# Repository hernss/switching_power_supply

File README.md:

# Descripción del proyecto:

El objetivo de este proyecto es desarrollar una fuente switching de voltaje variable basada en el integrado TPS54331 de Texas Instruments. Como entrada vamos a poder utilizar una fuente ATX estándar de PC o una fuentes del estilo notebook de hasta 24 volts. La fuente proveerá una salida variable entre 1.5 volts y 24 volts la cual es ajustada mediante un potenciómetro. En el caso de alimentarse con una fuente ATX también se va a disponer de las salidas de 3,3v +5v + 12v -5v -12v.
La salida esta implementadas con borneras en dos piezas, quedando el macho adherido al PCB y una parte removible a la cual se podrán conectar cables mediante tornillos.

# Calculo de los componentes:
## Bloqueo por bajo voltaje de entrada:

* R1=  (V_START- V_STOP)/(3µA)=(6.8V-6.5V)/(3µA)=100KΩ
* R2=V_EN/((V_START- V_EN)/R1+1µA)=1.25V/((6.8V-1.25V)/100KΩ+1µA)=22123Ω

Asumo R2 = 22KΩ

## Arranque Suave:

T_SS (ms)=(C_SS (nF)x V_REF (V))/(I_SS (mA))=(10 x 0.8)/2=4 ms

## Calculo de R5 y R6:

Según la hoja de datos recomienda utilizar una resistencia de alrededor de 10K para R5, por esto asumimos inicialmente a R5 como 10K

R6 la calculamos según la siguiente ecuación:

R6=(R5 x V_REF)/(V_OUT-V_REF )

## Para obtener 4.5V a la salida:

R6=(10KΩ x 0.8V)/(4.5V-0.8V)=2162Ω 

Asumo R6 = 2.2KΩ por ser el valor comercial más cercano.

V_OUT=V_REF  x (R5/R6+1)=0.8V x (10KΩ/2.2KΩ+1)=4.44V

## Para obtener 6V a la salida:
R6=(10KΩ x 0.8V)/(6V-0.8V)=1538Ω

Como el valor comercial más cercano está muy lejos del valor que necesitamos vamos a cambiar R5 a 12K y vamos a repetir los cálculos.

R6=(12KΩ x 0.8V)/(6V-0.8V)=1845Ω

Asumo R6 = 1,8KΩ  por ser el valor comercial más cercano.

V_OUT=V_REF  x (R5/R6+1)=0.8V x (12KΩ/1.8KΩ+1)=6.13V

## Valores máximos y mínimos de la tensión de salida:

Si ahora tomamos fijo R5 = 10K y agregamos un potenciómetro de 10K con una resistencia de 330Ω en serie podemos calcular el voltaje máximo y mínimo que podemos tener a la salida.

V_MAX=V_REF  x (R5/〖R6〗_MIN +1)=0.8V x (10KΩ/330Ω+1)=25.04V

V_MIN=V_REF  x (R5/〖R6〗_MAX +1)=0.8V x (10KΩ/10330Ω+1)=1.57V

Cabe aclarar que para obtener el VMAX a la salida, la entrada tiene que tener el voltaje suficiente.

# Diagrama Esquemático:

# Circuito impreso

# Vista 3D de la placa terminada

# Panelizado del PCB

# Diseño del gabinete

# Link a ON-Shape:

https://cad.onshape.com/documents/020dfdbda6882e2ac2e1fa2c/w/ac47c3931b7ff00251a716d9/e/94a10833bc3fe93f9d4dad91

# Lista de Materiales (BOM):

Cantidad	Referencia	Fabricante	Fabricante P/N	Digikey P/N

1	C1	Panasonic Electronic Components	EEE-HB1V100R	PCE4153CT-ND

1	C2	AVX Corporation	08055C104KAT2A	478-1395-1-ND

2	C3, C4	Yageo	CC0805KRX7R9BB103	311-1136-1-ND

1	C5	Samsung Electro-Mechanics	CL21B102KBANNNC	1276-1020-1-ND

1	C6	Samsung Electro-Mechanics	CL21C470JBANNNC	1276-1156-1-ND

1	C7	KEMET	T491X107K025AT	399-8410-1-ND

3	D1, D2, D3	Diodes Incorporated	B340B-13-F	B340B-FDICT-ND

1	D4	Lite-On Inc.	LTST-C170KGKT	160-1414-1-ND

1	D5	Lite-On Inc.	LTST-C171KRKT	160-1427-2-ND

1	J1	CUI Devices	PJ-002A	CP-002A-ND

1	J2	Molex	39299242	WM7334-ND

2	J3, J6	TE Connectivity AMP Connectors	796644-2	A98248-ND

2	J4, J5	TE Connectivity AMP Connectors	796644-3	A98249-ND

1	L1	Bourns Inc.	SRR1260-150M	SRR1260-150MCT-ND

2	MP1, MP2	Visual Communications Company	LFB063CTP	LFB063CTP-ND

1	R1	Yageo	RC0805JR-07100KL	311-100KARCT-ND

1	R2	Yageo	RC0805JR-0722KL	311-22KARCT-ND

1	R3	Yageo	RC0805FR-0729K4L	311-29.4KCRTR-ND

3	R4, R6, R7	Yageo	RC0805JR-07330RL	311-330RARCT-ND

1	R5	Yageo	RC0805JR-0710KL	311-10KARCT-ND

1	RV1	Bourns Inc.	PTV111-3415A-B103	PTV111-3415A-B103-ND

1	SW1	E-Switch	TL2230EEF140	EG6031-ND

1	U1	Texas Instruments	TPS54331DDAR	296-39419-1-ND

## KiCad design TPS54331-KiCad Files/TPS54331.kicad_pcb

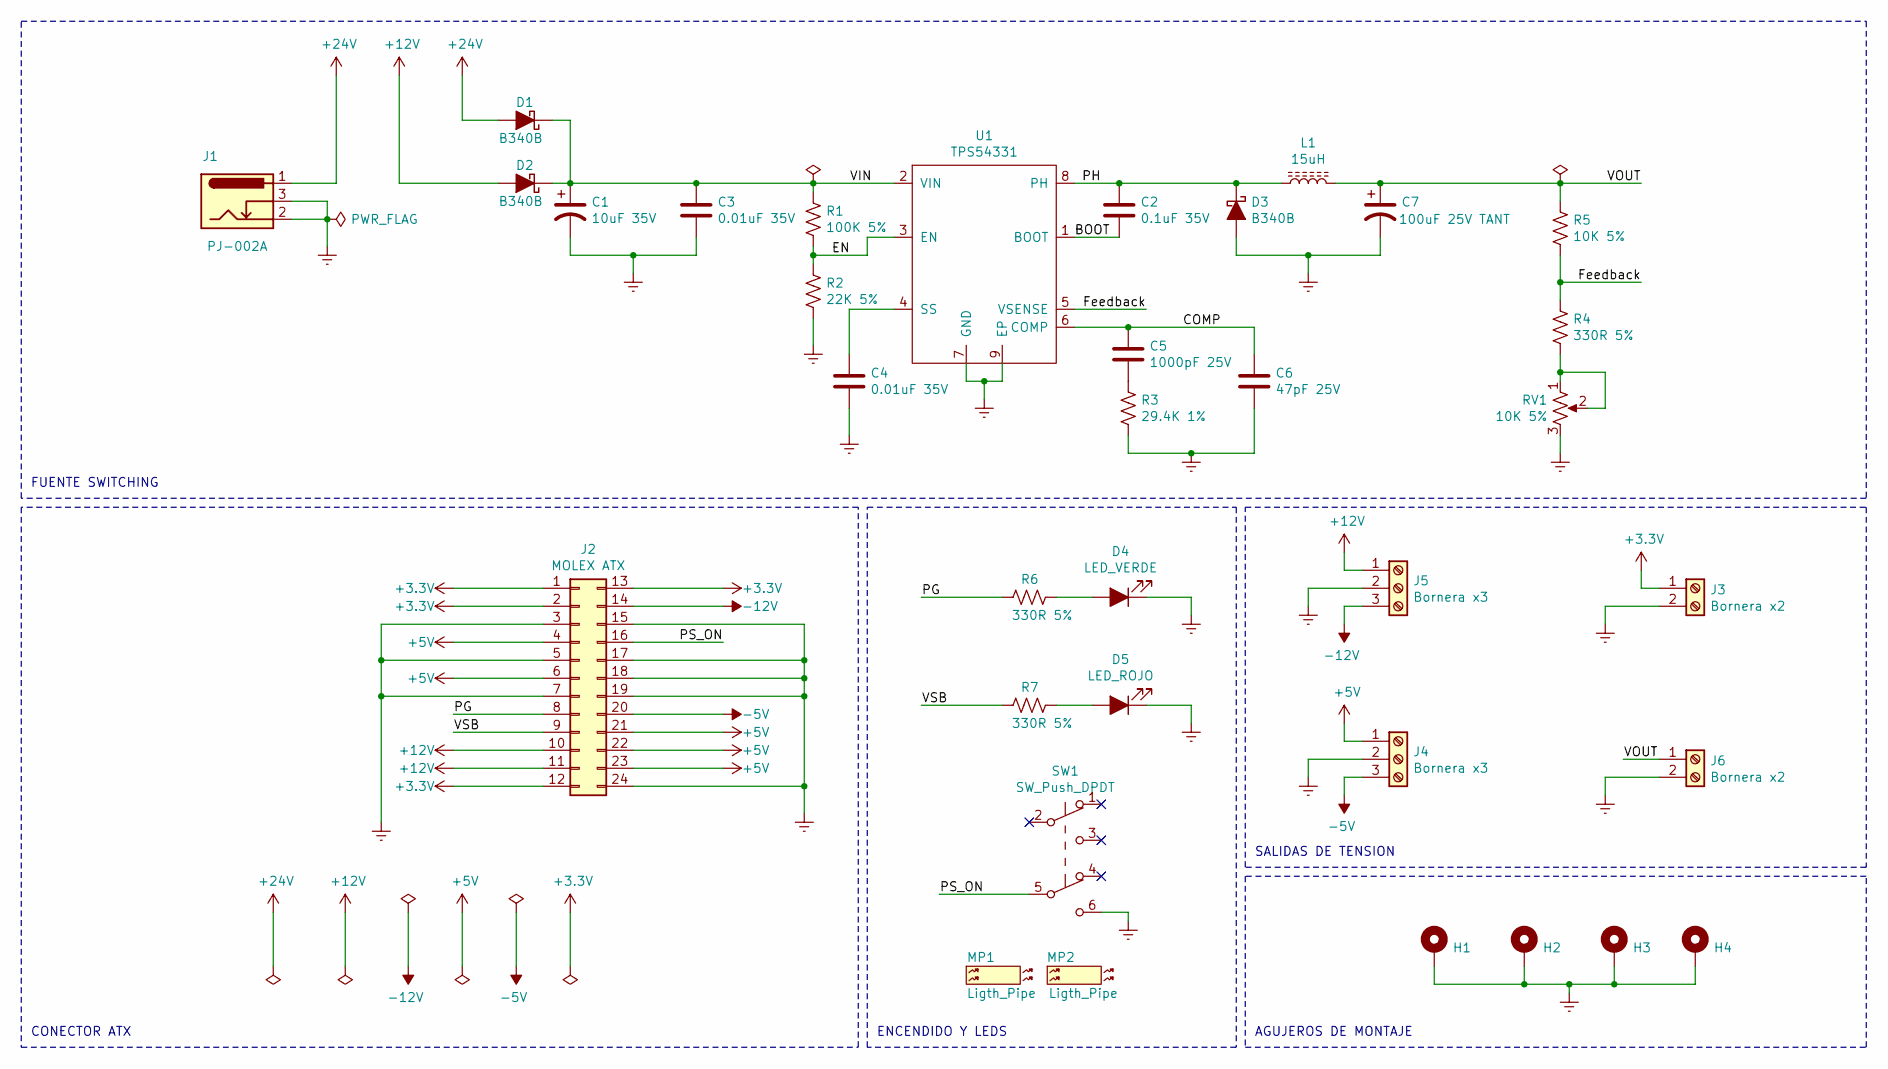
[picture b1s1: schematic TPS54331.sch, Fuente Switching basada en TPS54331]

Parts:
C1: 10uF 35V; CP_Elec_5x5.8; Manufacturer P/N EEE-HB1V100R; Digikey P/N PCE4153CT-ND
C2: 0.1uF 35V; C_0805_2012Metric; Manufacturer P/N 08055C104KAT2A; Digikey P/N 478-1395-1-ND
C3, C4: 0.01uF 35V; C_0805_2012Metric; Manufacturer P/N CC0805KRX7R9BB103; Digikey P/N 311-1136-1-ND
C5: 1000pF 25V; C_0805_2012Metric; Manufacturer P/N CL21B102KBANNNC; Digikey P/N 1276-1020-1-ND
C6: 47pF 25V; C_0805_2012Metric; Manufacturer P/N CL21C470JBANNNC; Digikey P/N 1276-1156-1-ND
C7: 100uF 25V TANT; CP_EIA-7343-43_Kemet-X; Manufacturer P/N T491X107K025AT; Digikey P/N 399-8410-1-ND
D1, D2, D3: B340B; D_SMB; Manufacturer P/N B340B-13-F; Digikey P/N B340B-FDICT-ND
D4: LED_VERDE; LED_0805_2012Metric; Manufacturer P/N LTST-C170KGKT; Digikey P/N 160-1414-1-ND
D5: LED_ROJO; LED_0805_2012Metric; Manufacturer P/N LTST-C171KRKT; Digikey P/N 160-1427-2-ND
H1, H2, H3, H4: MountingHole_Pad; MountingHole_3.2mm_M3_Pad
J1: PJ-002A; Manufacturer P/N PJ-002A; Digikey P/N CP-002A-ND
J2: MOLEX ATX; Molex_0039301240; Manufacturer P/N 0039299242; Digikey P/N WM7334-ND
J3, J6: Bornera x2; 796644-2; Manufacturer P/N 796644-2; Digikey P/N A98248-ND
J4, J5: Bornera x3; 796644-3; Manufacturer P/N 796644-3; Digikey P/N A98249-ND
L1: 15uH; SRR1260; Manufacturer P/N SRR1260-150M; Digikey P/N SRR1260-150MCT-ND
MP1, MP2: Ligth_Pipe; NoFootprint; Manufacturer P/N LFB063CTP; Digikey P/N LFB063CTP-ND
R1: 100K 5%; R_0805_2012Metric; Manufacturer P/N RC0805JR-07100KL; Digikey P/N 311-100KARCT-ND
R2: 22K 5%; R_0805_2012Metric; Manufacturer P/N RC0805JR-0722KL; Digikey P/N 311-22KARCT-ND
R3: 29.4K 1%; R_0805_2012Metric; Manufacturer P/N RC0805FR-0729K4L; Digikey P/N 311-29.4KCRTR-ND
R4, R6, R7: 330R 5%; R_0805_2012Metric; Manufacturer P/N RC0805JR-07330RL; Digikey P/N 311-330RARCT-ND
R5: 10K 5%; R_0805_2012Metric; Manufacturer P/N RC0805JR-0710KL; Digikey P/N 311-10KARCT-ND
RV1: 10K 5%; PTV111-3; Manufacturer P/N PTV111-3415A-B103; Digikey P/N PTV111-3415A-B103-ND
SW1: SW_Push_DPDT; TL2230; Manufacturer P/N TL2230EEF140; Digikey P/N EG6031-ND
U1: TPS54331; SOIC-8-1EP_3.9x4.9mm_P1.27mm_EP2.29x3mm; Manufacturer P/N TPS54331DDAR; Digikey P/N 296-39419-1-ND

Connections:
+3V3: J2.1, J2.2, J2.12, J2.13, J3.1
+5V: J2.4, J2.6, J2.21, J2.22, J2.23, J4.1
+12V: D2.2 (A), J2.10, J2.11, J5.1
+24V: D1.2 (A), J1.1
-5V: J2.20, J4.3
-12V: J2.14, J5.3
/BOOT: C2.2, U1.1 (BOOT)
/COMP: C5.1, C6.1, U1.6 (COMP)
/EN: R1.2, R2.1, U1.3 (EN)
/Feedback: R4.1, R5.2, U1.5 (VSENSE)
/PG: J2.8, R6.2
/PH: C2.1, D3.1 (K), L1.1, U1.8 (PH)
/PS_ON: J2.16, SW1.5 (B)
/VIN: C1.1, C3.1, D1.1 (K), D2.1 (K), R1.1, U1.2 (VIN)
/VOUT: C7.1, J6.1, L1.2, R5.1
/VSB: J2.9, R7.2
Earth: C1.2, C3.2, C4.2, C6.2, C7.2, D3.2 (A), D4.1 (K), D5.1 (K), H1.1, H2.1, H3.1, H4.1, J1.2, J1.3, J2.3, J2.5, J2.7, J2.15, J2.17, J2.18, J2.19, J2.24, J3.2, J4.2, J5.2, J6.2, R2.2, R3.2, RV1.3, SW1.6 (C), U1.7 (GND), U1.9 (EP)
unnamed: C4.1, U1.4 (SS)
unnamed: C5.2, R3.1
unnamed: D4.2 (A), R6.1
unnamed: D5.2 (A), R7.1
unnamed: R4.2, RV1.1, RV1.2

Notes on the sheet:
ENCENDIDO Y LEDS
CONECTOR ATX
FUENTE SWITCHING
SALIDAS DE TENSION
AGUJEROS DE MONTAJE

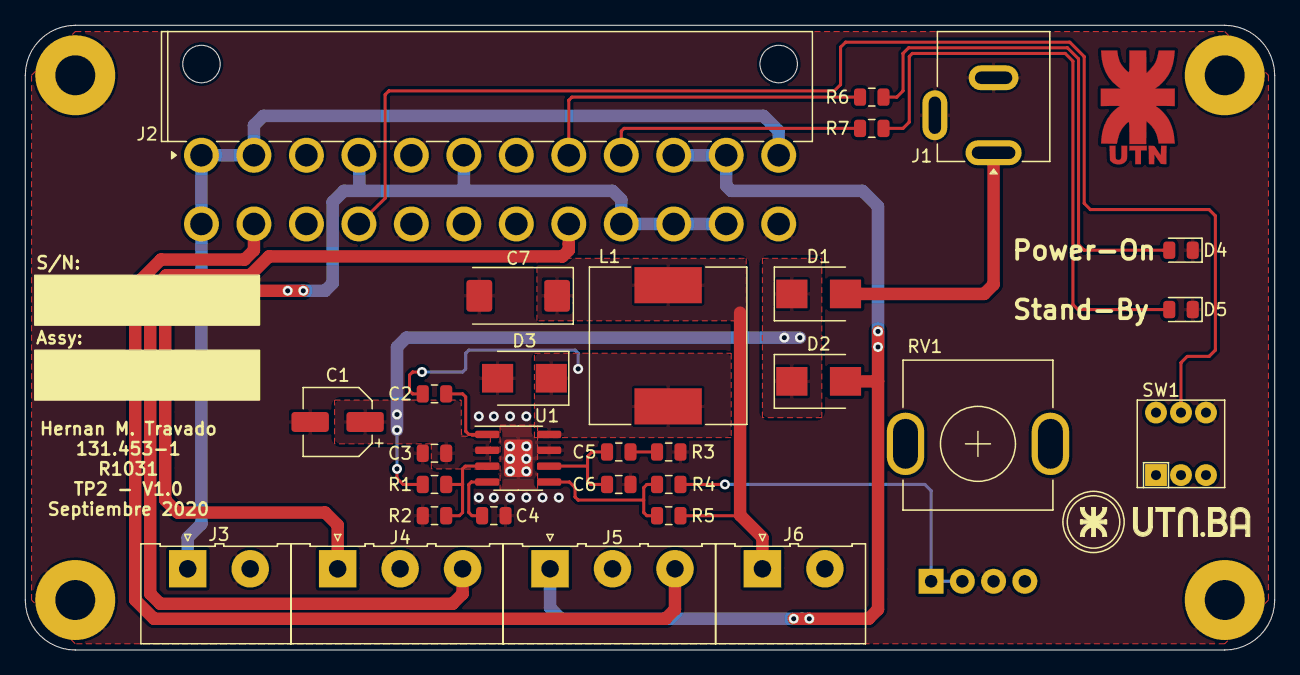
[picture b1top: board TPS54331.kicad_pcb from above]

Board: 2 copper layers, 100.0 x 50.0 mm, 36 parts (0 on the bottom side), 22 nets.

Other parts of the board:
LogoUTN.BA-Letras: UTN.BA-Letras

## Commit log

2023-02-13 Readme Update
